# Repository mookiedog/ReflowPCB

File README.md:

# Toaster Oven Reflow Controller

This project creates a daughterboard for a [Sparkfun Artemis Redboard](https://www.sparkfun.com/products/15444) that acts as a toaster oven reflow controller. The software required to drive the daughterboard is its own Github project, located [here](https://github.com/mookiedog/Reflow).

It is not necessary to use a Redboard with this daughterboard - pretty much any Arduino with the same daughterboard connectors will work. You would need to write your own software though. Honestly, the software can be pretty trivial. The software project for the Redboard is perhaps needlessly complex just so that it can drive a small LCD with lots of information regarding the ongoing reflow process.

If you do not have Eagle, or just want to fabricate a PCB based on this design, a prebuilt zip file exists containing everything required to get the PCB fabricated at [JLCPCB.com](https://jlcpcb.com/). 

As of Feb 2023, the current release version of the reflow controller is 1V2.

To get a PCB built using the zip file, perform the following steps:
1. Download the zip file to your machine
1. Go to the [JLCPCB.com](https://jlcpcb.com/) website.
1. Click on the 'Instant Quote' button
1. Drag the zip file onto the button marked 'Add Gerber File'. There is a button to view the Gerbers. If you click it and then look at the top or bottom layers, you should see something like this:

1. Once the board uploads, you can choose various production options. The default production selections should be just fine, such as:
    1. PCB color
    1. HASL (with lead)

    The only option you might want is for "remove order number": specify 'select location'. This tells JCLPCB to put the order number that JCLPCB silkscreens onto all the boards in an innocuous location. The board files in the zip file already specify where to place the order number so all you need to do is click 'select location'.
1. Click 'save to cart', then go through the order process. It is pretty self-explanitory.

The hardest part is waiting 2 weeks for the boards to arrive!

## Oven

Obviously, you will need a toaster oven to go with this project. I recommend any oven that has 4 heating elements (2 lower, 2 upper) plus a circulating fan. I suspect that pretty much any oven would work, but some small software changes would be required.

# As Always

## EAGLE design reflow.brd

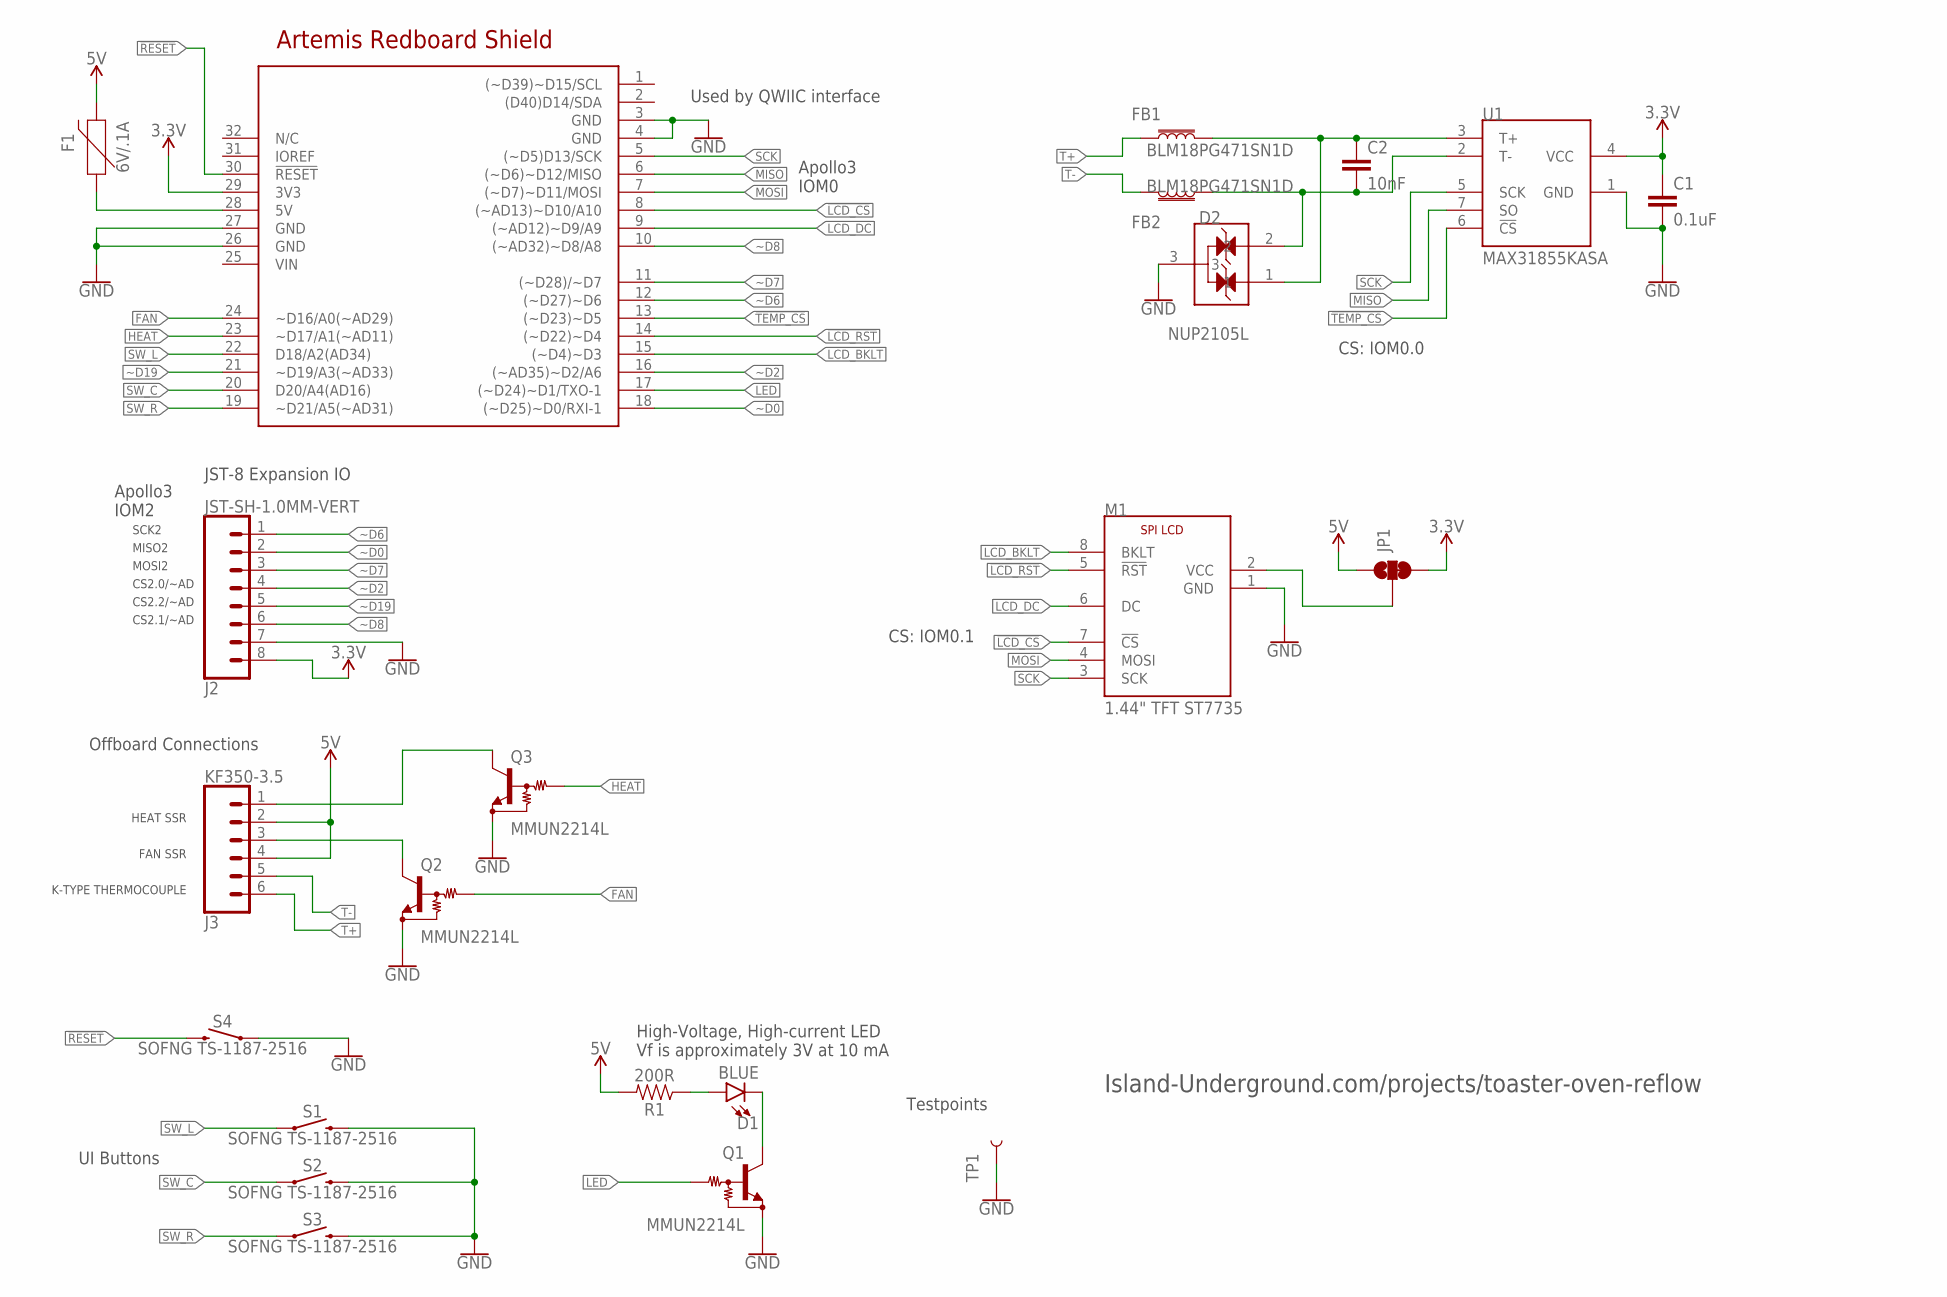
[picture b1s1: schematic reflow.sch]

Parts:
C1: 0.1uF; 0603
C2: 10nF; 0603
D1: BLUE; LED-0603
D2: NUP2105L; SOT23
F1: 6V/.1A; 1206
FB1, FB2: BLM18PG471SN1D; 0603
J2: JST-SH-1.0MM-VERT; JST-SH-1.0MM-8V
J3: KF350-3.5; SCREWTERMINAL-3.5MM-6
JP1: JUMPER-SMT_3_1-NC_TRACE_SILK; SMT-JUMPER_3_1-NC_TRACE_SILK
M1: 1.44" TFT ST7735; LCD-SPI-1P44
Q1, Q2, Q3: MMUN2214L; SOT23
R1: 200R; 0603
S1, S2, S3, S4: SOFNG TS-1187-2516; SWITCH-TAC-5.2
TP1: TESTPOINT-KEYSTONE-1035; KEYSTONE-1035
U1: MAX31855KASA; SOIC-8
U$1: ARTEMIS_REDBOARD_SHIELD

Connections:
3.3V: C1.1, J2.8, JP1.3, U1.4 (VCC), U$1.29 (3V3)
5V: F1.2, J3.2, J3.4, JP1.1, R1.2
!LCD_CS: M1.7 (!CS), U$1.8 ((~AD13)~D10/A10)
!LCD_RST: M1.5 (!RST), U$1.14 ((~D22)~D4)
!RESET: S4.2@1 (2), S4.2@2 (2), U$1.30 (!RESET)
!TEMP_CS: U1.6 (!CS), U$1.13 ((~D23)~D5)
FAN: Q2.1 (B), U$1.24 (~D16/A0(~AD29))
GND: C1.2, D2.3, J2.7, M1.1 (GND), Q1.2 (E), Q2.2 (E), Q3.2 (E), S1.2@1 (2), S1.2@2 (2), S2.2@1 (2), S2.2@2 (2), S3.2@1 (2), S3.2@2 (2), S4.1@1 (1), S4.1@2 (1), TP1.P$1, U1.1 (GND), U$1.3 (GND), U$1.4 (GND), U$1.26 (GND), U$1.27 (GND)
HEAT: Q3.1 (B), U$1.23 (~D17/A1(~AD11))
LCD_BKLT: M1.8 (BKLT), U$1.15 ((~D4)~D3)
LCD_DC: M1.6 (DC), U$1.9 ((~AD12)~D9/A9)
LED: Q1.1 (B), U$1.17 ((~D24)~D1/TXO-1)
MISO: U1.7 (SO), U$1.6 ((~D6)~D12/MISO)
MOSI: M1.4 (MOSI), U$1.7 ((~D7)~D11/MOSI)
unnamed: D1.C, Q1.3 (C)
unnamed: D1.A, R1.1
unnamed: F1.1, U$1.28 (5V)
unnamed: J3.3, Q2.3 (C)
unnamed: JP1.2, M1.2 (VCC)
unnamed: J3.1, Q3.3 (C)
unnamed: C2.1, D2.1, FB1.2, U1.3 (T+)
unnamed: C2.2, D2.2, FB2.1, U1.2 (T-)
SCK: M1.3 (SCK), U1.5 (SCK), U$1.5 ((~D5)D13/SCK)
SW_C: S2.1@1 (1), S2.1@2 (1), U$1.20 (D20/A4(AD16))
SW_L: S1.1@1 (1), S1.1@2 (1), U$1.22 (D18/A2(AD34))
SW_R: S3.1@1 (1), S3.1@2 (1), U$1.19 (~D21/A5(~AD31))
T+: FB1.1, J3.6
T-: FB2.2, J3.5
~D0: J2.2, U$1.18 ((~D25)~D0/RXI-1)
~D2: J2.4, U$1.16 ((~AD35)~D2/A6)
~D6: J2.1, U$1.12 ((~D27)~D6)
~D7: J2.3, U$1.11 ((~D28)/~D7)
~D8: J2.6, U$1.10 ((~AD32)~D8/A8)
~D19: J2.5, U$1.21 (~D19/A3(~AD33))

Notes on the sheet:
CS: IOM0.1
UI Buttons
SCK2
MISO2
MOSI2
CS2.0/~AD
CS2.2/~AD
CS2.1/~AD
Apollo3 IOM2
JST-8 Expansion IO
Used by QWIIC interface
Offboard Connections
HEAT SSR
FAN SSR
K-TYPE THERMOCOUPLE
High-Voltage, High-current LED Vf is approximately 3V at 10 mA
Testpoints
Apollo3 IOM0
Island-Underground.com/projects/toaster-oven-reflow
CS: IOM0.0

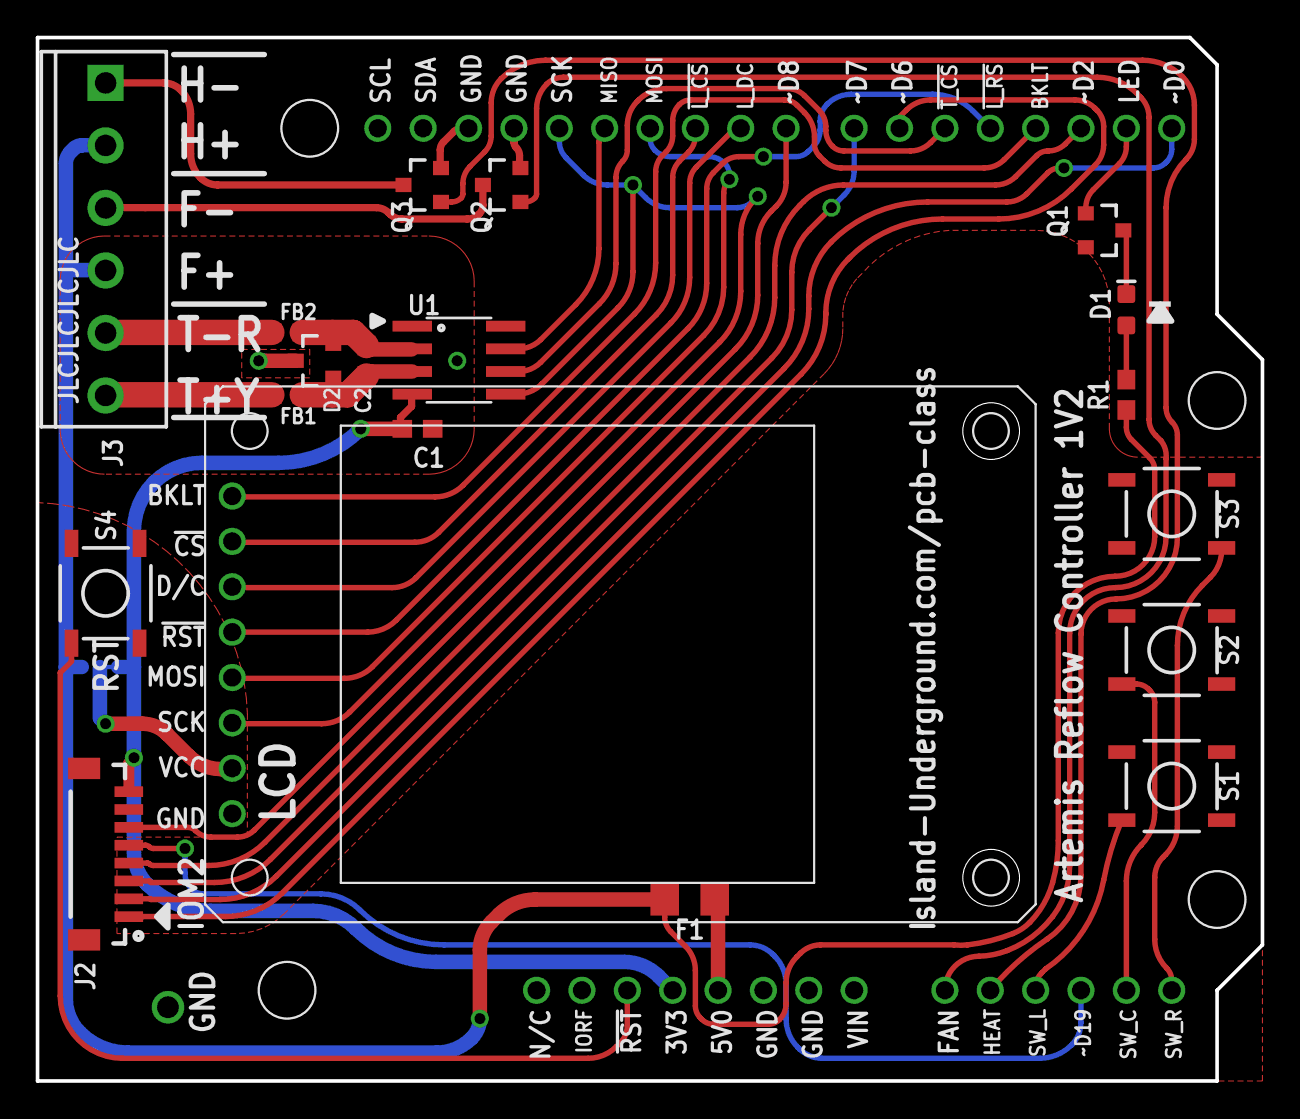
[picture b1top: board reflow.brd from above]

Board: 2 copper layers, 68.6 x 58.4 mm, 22 parts (1 on the bottom side), 34 nets.

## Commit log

2023-02-12 Add the BOM

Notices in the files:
parts and their libraries:
SparkFun-Connectors: Licensing: Creative Commons ShareAlike 4.0 International - https://creativecommons.org/licenses/by-sa/4.0
